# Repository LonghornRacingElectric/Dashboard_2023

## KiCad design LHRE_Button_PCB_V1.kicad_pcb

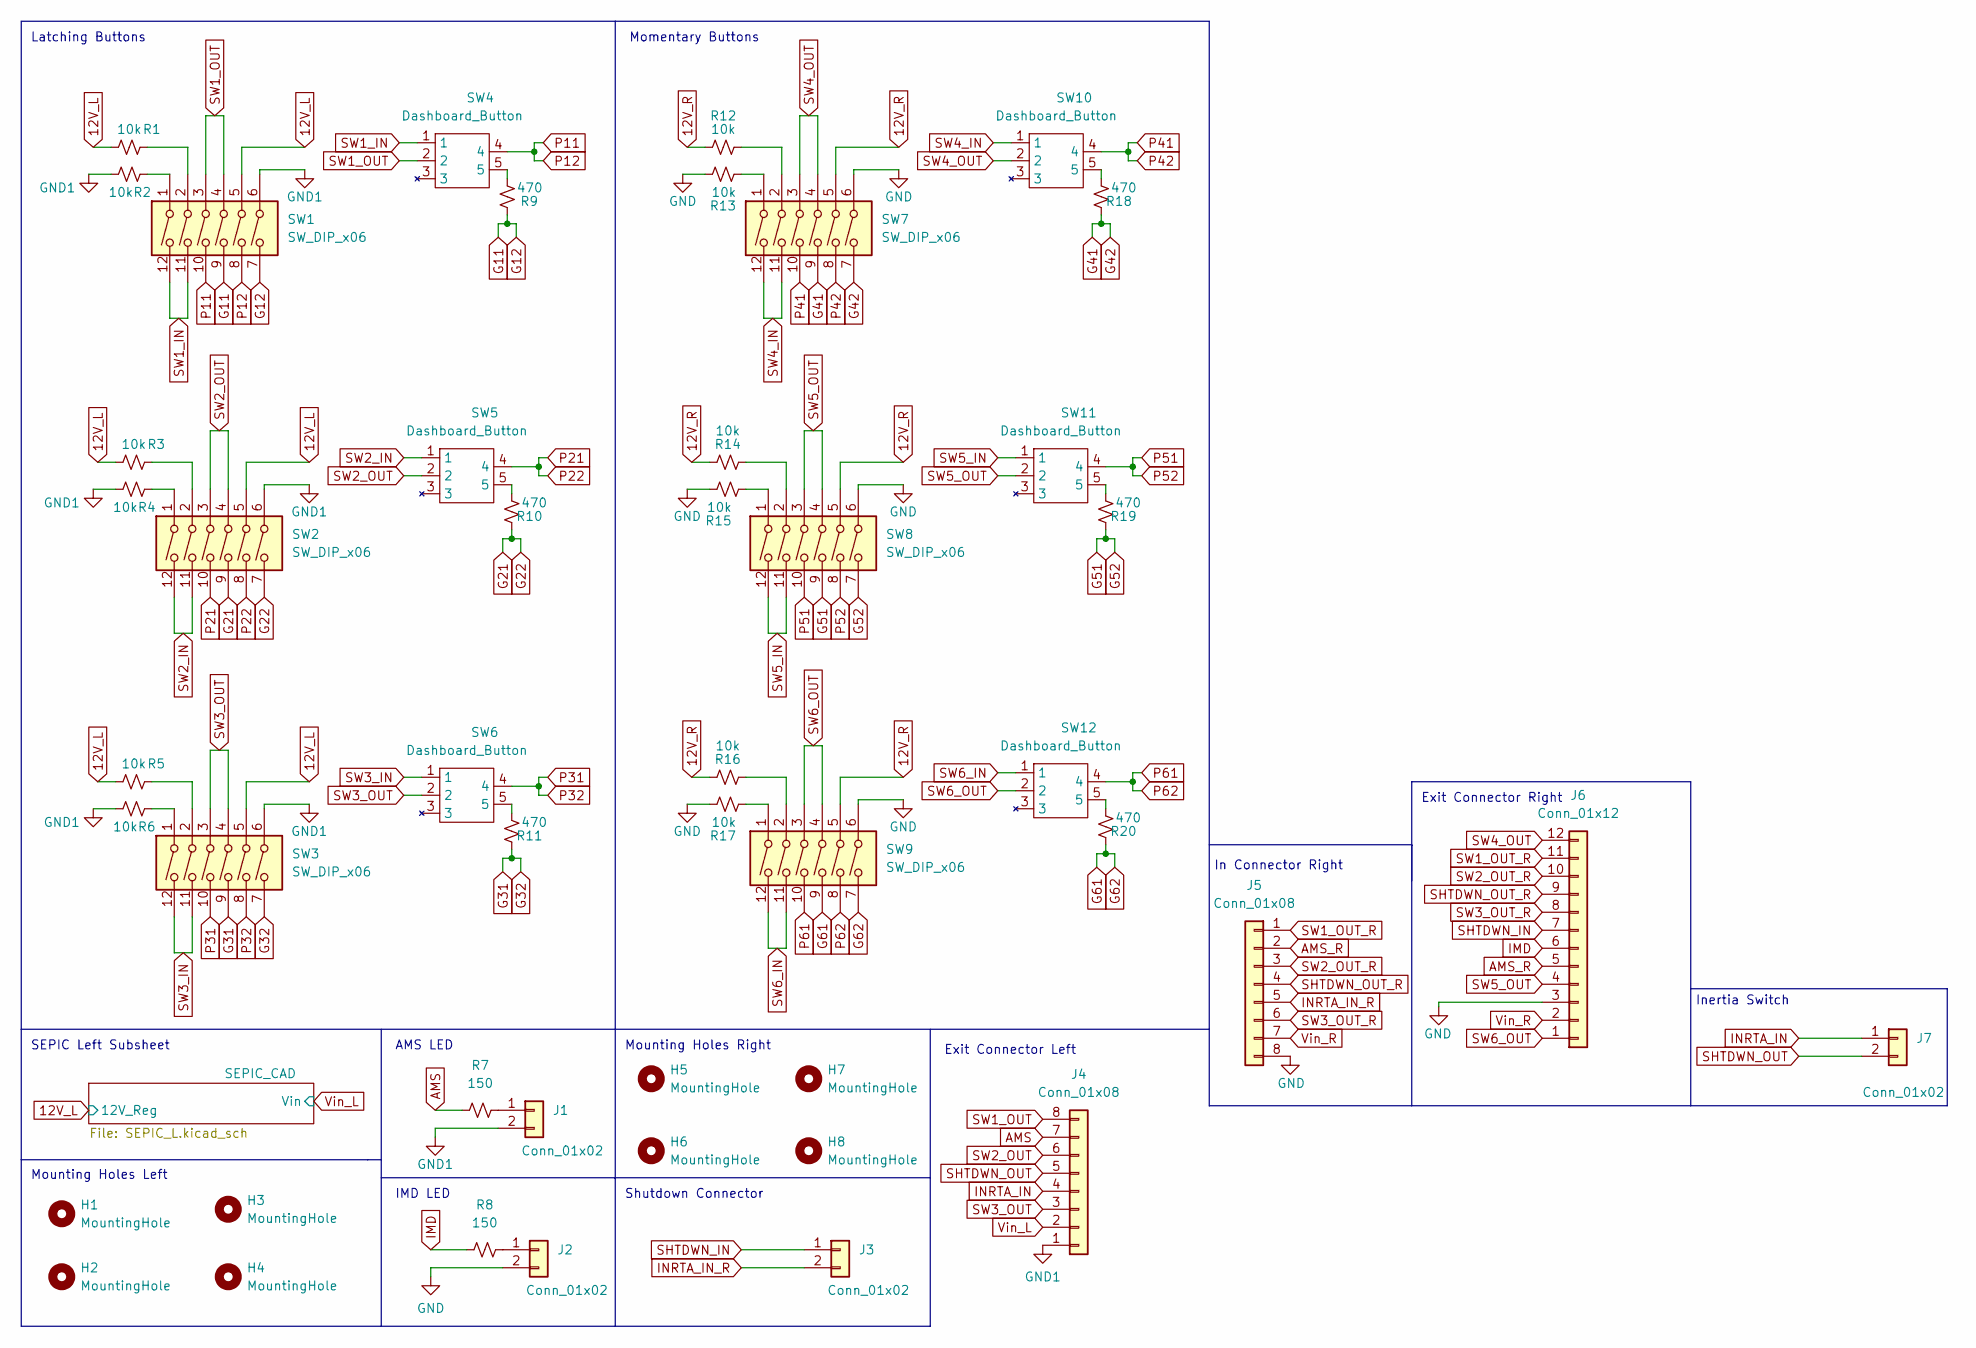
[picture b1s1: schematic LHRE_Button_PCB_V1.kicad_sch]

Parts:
H1, H2, H3, H4, H5, H6, H7, H8: MountingHole; MountingHole_3.5mm
J1, J2, J3, J7: Conn_01x02; Molex_Micro-Fit_3.0_43650-0215_1x02_P3.00mm_Vertical
J4, J5: Conn_01x08; Molex_Micro-Fit_3.0_43650-0800_1x08_P3.00mm_Horizontal
J6: Conn_01x12; Molex_Micro-Fit_3.0_43045-1212_2x06_P3.00mm_Vertical
R1, R2, R3, R4, R5, R6, R12, R13, R14, R15, R16, R17: 10k; R_0603_1608Metric_Pad0.98x0.95mm_HandSolder
R7, R8: 150; R_0603_1608Metric_Pad0.98x0.95mm_HandSolder
R9, R10, R11, R18, R19, R20: 470; R_0603_1608Metric_Pad0.98x0.95mm_HandSolder
SW1, SW2, SW3, SW7, SW8, SW9: SW_DIP_x06; 18253604
SW4, SW5, SW6, SW10, SW11, SW12: Dashboard_Button; Dashboard_Btn

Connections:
12V_L: R1.1, R3.1, R5.1, SW1.5, SW2.5, SW3.5; also elsewhere on the board
12V_R: R12.1, R14.1, R16.1, SW7.5, SW8.5, SW9.5
AMS: J4.7, R7.1
AMS_R: J5.2, J6.5
G11: R9.1, SW1.7, SW1.9
G21: R10.1, SW2.7, SW2.9
G31: R11.1, SW3.7, SW3.9
G41: R18.1, SW7.7, SW7.9
G51: R19.1, SW8.7, SW8.9
G61: R20.1, SW9.7, SW9.9
GND: J2.2, J5.8, J6.3, R13.1, R15.1, R17.1, SW7.6, SW8.6, SW9.6
GND1: J1.2, J4.1, R2.1, R4.1, R6.1, SW1.6, SW2.6, SW3.6; also elsewhere on the board
IMD: J6.6, R8.1
INRTA_IN: J4.4, J7.1
INRTA_IN_R: J3.2, J5.5
unnamed: J1.1, R7.2
unnamed: J2.1, R8.2
unnamed: R1.2, SW1.2
unnamed: R2.2, SW1.1
unnamed: R3.2, SW2.2
unnamed: R4.2, SW2.1
unnamed: R5.2, SW3.2
unnamed: R6.2, SW3.1
unnamed: R9.2, SW4.5
unnamed: R10.2, SW5.5
unnamed: R11.2, SW6.5
unnamed: R12.2, SW7.2
unnamed: R13.2, SW7.1
unnamed: R14.2, SW8.2
unnamed: R15.2, SW8.1
unnamed: R16.2, SW9.2
unnamed: R17.2, SW9.1
unnamed: R18.2, SW10.5
unnamed: R19.2, SW11.5
unnamed: R20.2, SW12.5
P11: SW1.8, SW1.10, SW4.4
P21: SW2.8, SW2.10, SW5.4
P31: SW3.8, SW3.10, SW6.4
P41: SW7.8, SW7.10, SW10.4
P51: SW8.8, SW8.10, SW11.4
P61: SW9.8, SW9.10, SW12.4
SHTDWN_IN: J3.1, J6.7
SHTDWN_OUT: J4.5, J7.2
SHTDWN_OUT_R: J5.4, J6.9
SW1_IN: SW1.11, SW1.12, SW4.1
SW1_OUT: J4.8, SW1.3, SW1.4, SW4.2
SW1_OUT_R: J5.1, J6.11
SW2_IN: SW2.11, SW2.12, SW5.1
SW2_OUT: J4.6, SW2.3, SW2.4, SW5.2
SW2_OUT_R: J5.3, J6.10
SW3_IN: SW3.11, SW3.12, SW6.1
SW3_OUT: J4.3, SW3.3, SW3.4, SW6.2
SW3_OUT_R: J5.6, J6.8
SW4_IN: SW7.11, SW7.12, SW10.1
SW4_OUT: J6.12, SW7.3, SW7.4, SW10.2
SW5_IN: SW8.11, SW8.12, SW11.1
SW5_OUT: J6.4, SW8.3, SW8.4, SW11.2
SW6_IN: SW9.11, SW9.12, SW12.1
SW6_OUT: J6.1, SW9.3, SW9.4, SW12.2
Vin_L: J4.2; also elsewhere on the board
Vin_R: J5.7, J6.2

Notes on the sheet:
Shutdown Connector
AMS LED
Exit Connector Right
In Connector Right
Mounting Holes Left
IMD LED
Inertia Switch
Momentary Buttons
Exit Connector Left
Mounting Holes Right
SEPIC Left Subsheet
Latching Buttons

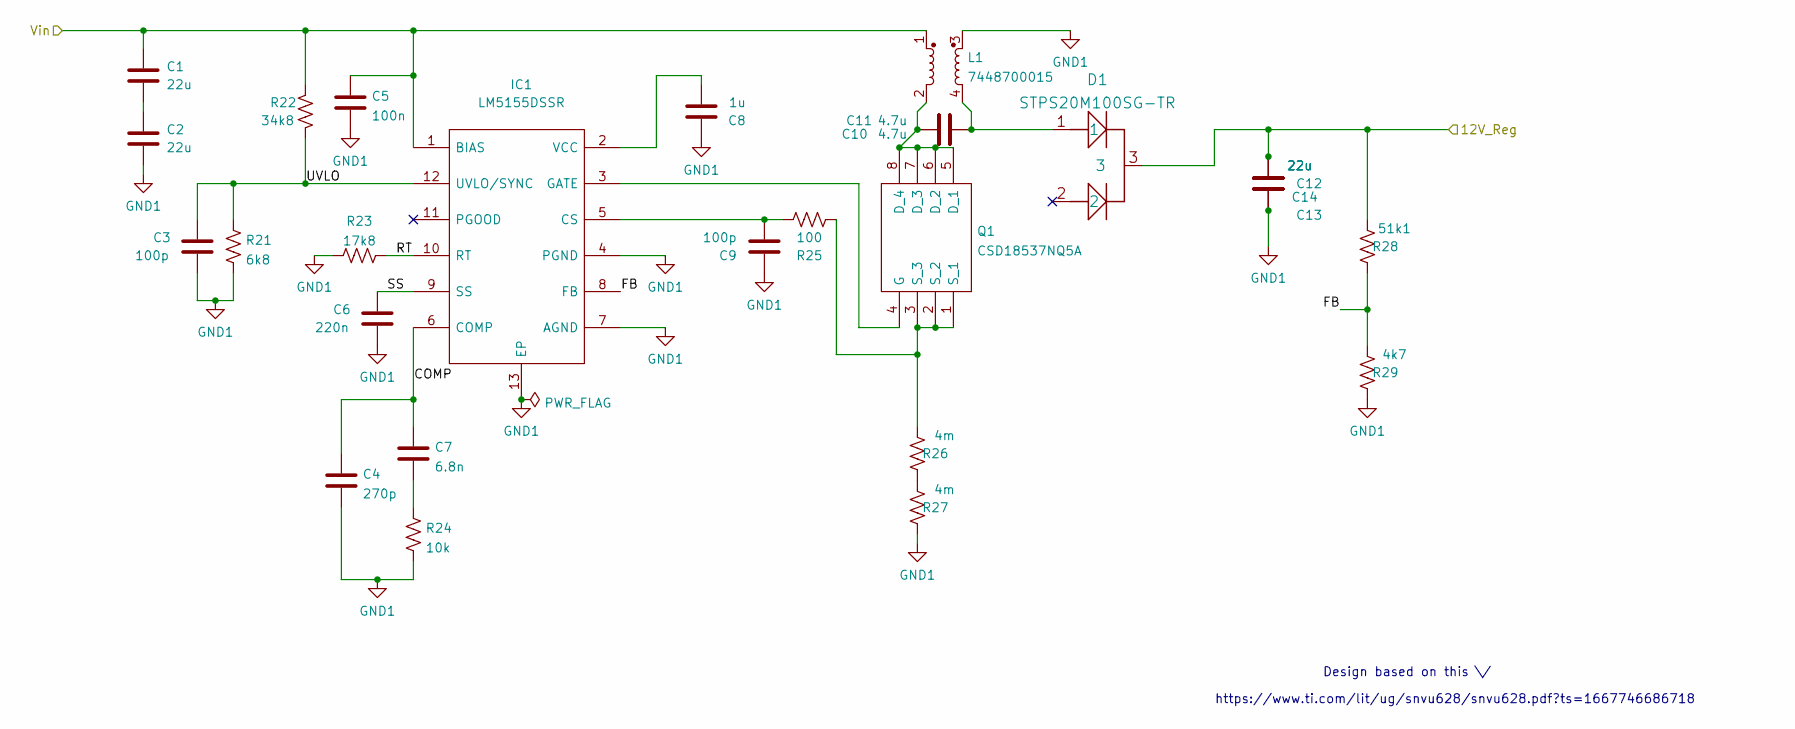
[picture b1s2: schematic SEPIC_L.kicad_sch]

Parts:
C1, C2, C12, C13, C14: 22u; C_1206_3216Metric_Pad1.33x1.80mm_HandSolder
C3, C9: 100p; C_0603_1608Metric_Pad1.08x0.95mm_HandSolder
C4: 270p; C_0603_1608Metric_Pad1.08x0.95mm_HandSolder
C5: 100n; C_0603_1608Metric_Pad1.08x0.95mm_HandSolder
C6: 220n; C_0603_1608Metric_Pad1.08x0.95mm_HandSolder
C7: 6.8n; C_0603_1608Metric_Pad1.08x0.95mm_HandSolder
C8: 1u; C_0805_2012Metric_Pad1.18x1.45mm_HandSolder
C10, C11: 4.7u; C_0805_2012Metric_Pad1.18x1.45mm_HandSolder
D1: STPS20M100SG-TR
IC1: LM5155DSSR; SON50P200X300X80-13N-D; Mouser Part Number 595-LM5155DSSR
L1: 7448700015; WE-DD_12XX_CROSSED12
Q1: CSD18537NQ5A; CSD19531Q5AT; Mouser Part Number 595-CSD18537NQ5A
R21: 6k8; R_0603_1608Metric_Pad0.98x0.95mm_HandSolder
R22: 34k8; R_0603_1608Metric_Pad0.98x0.95mm_HandSolder
R23: 17k8; R_0603_1608Metric_Pad0.98x0.95mm_HandSolder
R24: 10k; R_0603_1608Metric_Pad0.98x0.95mm_HandSolder
R25: 100; R_0603_1608Metric_Pad0.98x0.95mm_HandSolder
R26, R27: 4m; R_0603_1608Metric_Pad0.98x0.95mm_HandSolder
R28: 51k1; R_0603_1608Metric_Pad0.98x0.95mm_HandSolder
R29: 4k7; R_0603_1608Metric_Pad0.98x0.95mm_HandSolder

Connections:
12V_L: C12.1, C13.1, C14.1, D1.3, R28.1; also elsewhere on the board
/SEPIC_CAD/COMP: C4.1, C7.1, IC1.6 (COMP)
/SEPIC_CAD/FB: IC1.8 (FB), R28.2, R29.1
/SEPIC_CAD/RT: IC1.10 (RT), R23.2
/SEPIC_CAD/SS: C6.1, IC1.9 (SS)
/SEPIC_CAD/UVLO: C3.1, IC1.12 (UVLO/SYNC), R21.1, R22.2
GND1: C2.2, C3.2, C4.2, C5.2, C6.2, C8.1, C9.1, C12.2, C13.2, C14.2, IC1.4 (PGND), IC1.7 (AGND), IC1.13 (EP), L1.3, R21.2, R23.1, R24.2, R27.2, R29.2; also elsewhere on the board
unnamed: C1.2, C2.1
unnamed: C7.2, R24.1
unnamed: C8.2, IC1.2 (VCC)
unnamed: C9.2, IC1.5 (CS), R25.2
unnamed: C10.1, C11.1, D1.1, L1.4
unnamed: C10.2, C11.2, L1.2, Q1.5 (D_1), Q1.6 (D_2), Q1.7 (D_3), Q1.8 (D_4)
unnamed: IC1.3 (GATE), Q1.4 (G)
unnamed: Q1.1 (S_1), Q1.2 (S_2), Q1.3 (S_3), R25.1, R26.1
unnamed: R26.2, R27.1
Vin_L: C1.1, C5.1, IC1.1 (BIAS), L1.1, R22.1; also elsewhere on the board

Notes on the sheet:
https://www.ti.com/lit/ug/snvu628/snvu628.pdf?ts=1667746686718
Design based on this \/

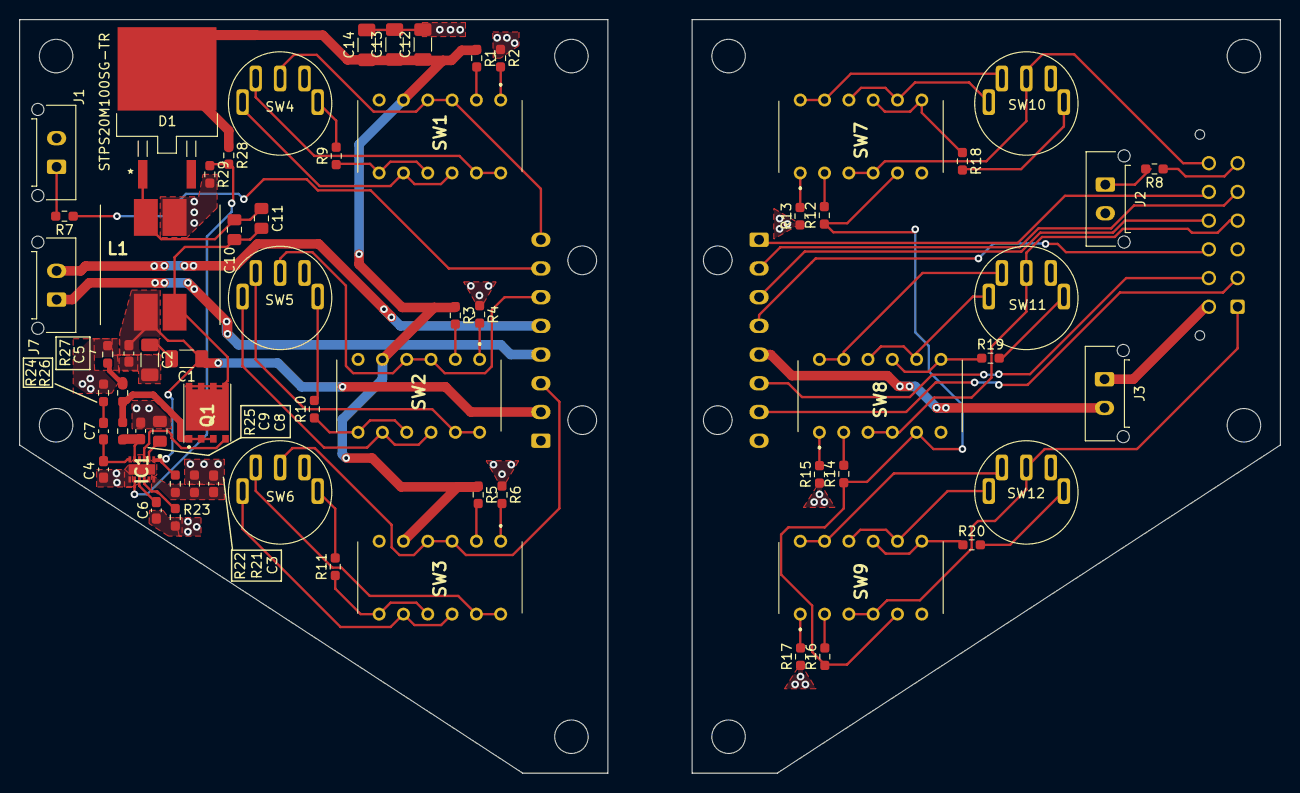
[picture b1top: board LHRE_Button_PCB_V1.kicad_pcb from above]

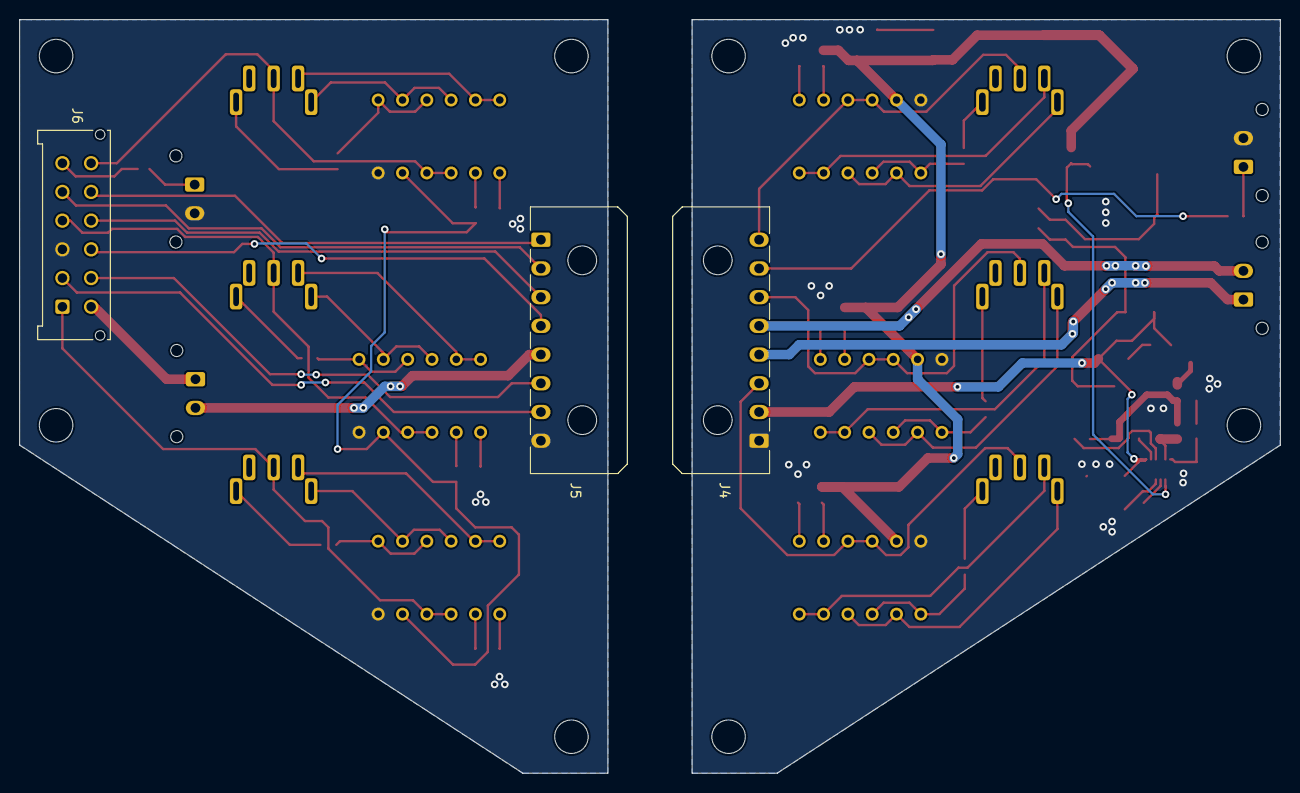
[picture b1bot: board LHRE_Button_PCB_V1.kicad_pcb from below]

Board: 2 copper layers, 131.7 x 78.7 mm, 74 parts (3 on the bottom side), 75 nets.

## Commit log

2022-09-26 Added 2023KicadLibrary
2022-11-27 second review dash
2022-12-04 try 1
2022-12-20 board proto
2022-12-20 board proto2
2022-12-20 board 3
2022-12-20 silkscreen change
2023-01-01 updated dash PCB
2023-01-01 edited silkscreen
2023-01-01 thing
2023-01-05 REV2
2023-01-08 flipped connectors
2023-01-09 changeed caps
2023-01-10 final commit hopefully

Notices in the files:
parts and their libraries:
Copyright 2021 Accelerated Designs. All rights reserved.
